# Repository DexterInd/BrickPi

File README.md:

BrickPi
=====

This project combines the brains of a Raspberry Pi with the brawn of a LEGO MINDSTORMS NXT.  Read more about it here:  http://www.dexterindustries.com/BrickPi

These files have been made available online through a [Creative Commons Attribution-ShareAlike 3.0](http://creativecommons.org/licenses/by-sa/3.0/) license.

## Compatibility
This repository is for the BrickPi and BrickPi+. For the BrickPi3 (hardware version 3.x.x) see the [BrickPi3 repository](https://github.com/DexterInd/BrickPi3).

## Getting Started
We've devoted some serious time to trying to make sure that it's easy to get started.  If you're lost, we would like to first direct you to our [website for the BrickPi](http://www.dexterindustries.com/BrickPi/getting-started/).

## Quick Install

In order to quick install the `BrickPi` repository, open up a terminal and type the following command:
```
sudo curl -kL dexterindustries.com/update_brickpi_plus | bash
```
The same command can be used for updating the `BrickPi` to the latest version.

## This Repository
This repository holds firmware and hardware designs, as well as software examples for Python, C, and Scratch.  

## Image for the SD Card
Our custom image for the Raspberry Pi makes using the BrickPi easy.  We've modified the standard Raspbian a little bit.  You can download the latest image here [on our getting started section.](https://www.dexterindustries.com/howto/install-raspbian-for-robots-image-on-an-sd-card/)

## Firmware
The board firmware is made in Arduino in order to make it super-hackable.  The firmware is written in Arduino 1.0 and can be uploaded via an ISP programmer.  It can also be uploaded with an Arduino Uno, with an adapter explained in this repository.

The board supports LEGO NXT motors, EV3 motors, and LEGO NXT sensors, as well as many of Dexter Industries sensors for LEGO Mindstorms.

[Dexter Industries](http://www.dexterindustries.com/)
[BrickPi for the Raspberry Pi](http://www.dexterindustries.com/BrickPi)

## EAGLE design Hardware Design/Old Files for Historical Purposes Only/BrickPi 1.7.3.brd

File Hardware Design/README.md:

BrickPi Hardware
=====

Read [more about the BrickPi here](http://www.dexterindustries.com/BrickPi)

These files have been made available online through a [Creative Commons Attribution-ShareAlike 3.0](http://creativecommons.org/licenses/by-sa/3.0/) license.

## Getting Started

We've devoted some effort to making sure that it's easy to get started.  If you're lost, we would like to first direct you to our [website for the BrickPi](http://www.dexterindustries.com/BrickPi/)

## This Repository

This repository only holds our latest hardware designs.  

[Dexter Industries](http://www.dexterindustries.com/)
[BrickPi](http://www.dexterindustries.com/BrickPi)

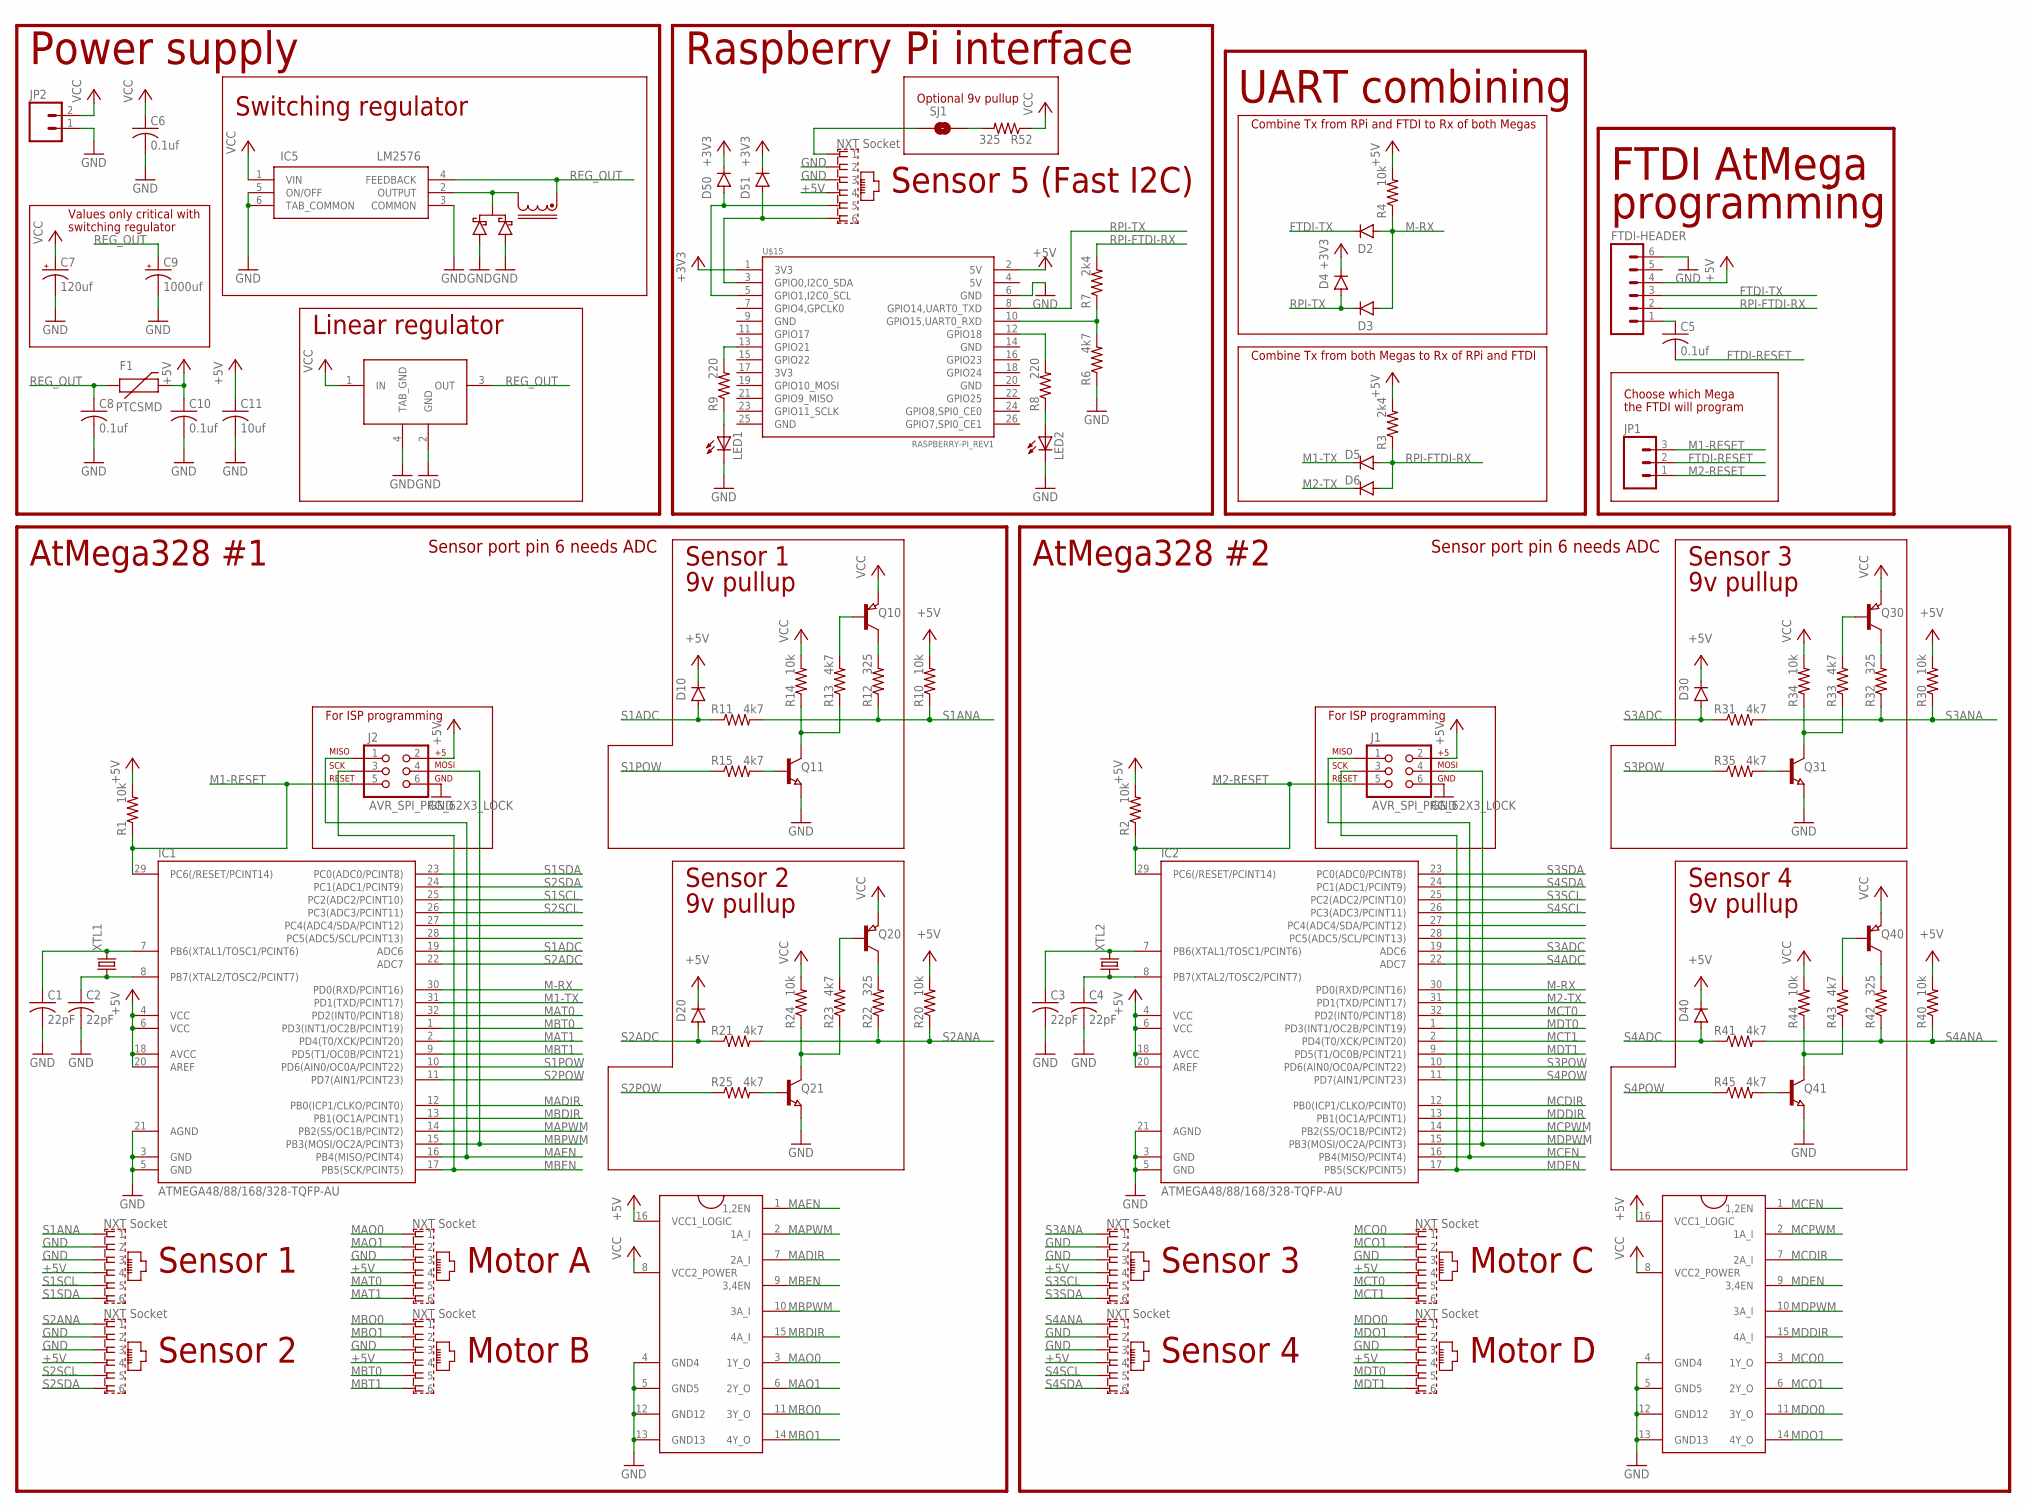
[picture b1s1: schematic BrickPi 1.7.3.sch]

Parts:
C1, C2, C3, C4: 22pF; C0805
C5, C6, C8, C10: 0.1uf; C0805
C7: 120uf; E2,5-6
C9: 1000uf; E3,5-10
C11: 10uf; C0805
D1: DIODE_SCHOTTKY_VS-6CWQ04FNTRPBF; DPAK
D2, D3, D4, D5, D6, D10, D20, D30, D40, D50, D51: DIODESOD80; SOD80
F1: PTCSMD; PTC-1206
FTDI-HEADER: M06LOCK; 1X06_LOCK
IC1, IC2: ATMEGA48/88/168/328-TQFP-AU; TQFP32-08
IC3, IC4: SN754410; DIL16-ROUND-HEAT_DIS_SN754410
IC5: LM2576; TO220-5-H
IC6: REGULATOR_5V_TO220-H_7805; TO220-H
J1, J2: AVR_SPI_PRG_62X3_LOCK; 2X3_LOCK
JP1: M03LOCK; 1X03_LOCK
JP2: M02LOCK; 1X02_LOCK
LED1, LED2: LED0805; 0805-LED
Q10, Q20, Q30, Q40: PNP-TRANSISTOR_SOT23; SOT23
Q11, Q21, Q31, Q41: NPN-TRANSISTOR_SOT23; SOT23
R1, R2, R4, R10, R14, R20, R24, R30, R34, R40, R44: 10k; 0603
R3, R7: 2k4; 0603
R6, R11, R13, R15, R21, R23, R25, R31, R33, R35, R41, R43, R45: 4k7; 0603
R8, R9: 220; 0603
R12, R22, R32, R42, R52: 325; 1206
SJ1: SOLDERJUMPERNO; SJ_2
U$3, U$4, U$5, U$7, U$8, U$9, U$10, U$11, U$12: NXT-SOCKETREGULAR; NXT-SOCKET
U$14: INDUCTOR_PULSE_P0250.XXXNL
U$15: RASPBERRY-PI_REV1
XTL1, XTL2: CRYSTALHC49S; HC49/S

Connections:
+3V3: D4.C, D50.C, D51.C, U$15.1 (3V3)
+5V: C10.1, C11.1, D10.C, D20.C, D30.C, D40.C, F1.2, FTDI-HEADER.4, IC1.4 (VCC), IC1.6 (VCC), IC1.18 (AVCC), IC1.20 (AREF), IC2.4 (VCC), IC2.6 (VCC), IC2.18 (AVCC), IC2.20 (AREF), IC3.16 (VCC1_LOGIC), IC4.16 (VCC1_LOGIC), J1.2, J2.2, R1.2, R2.2, R3.2, R4.2, R10.2, R20.2, R30.2, R40.2, U$3.4, U$4.4, U$5.4, U$7.4, U$8.4, U$9.4, U$10.4, U$11.4, U$12.4, U$15.2 (5V)
FTDI-RESET: C5.2, JP1.2
FTDI-TX: D2.C, FTDI-HEADER.3
GND: C1.2, C2.2, C3.2, C4.2, C6.2, C7.-, C8.2, C9.-, C10.2, C11.2, D1.1, D1.3, FTDI-HEADER.6, IC1.3 (GND), IC1.5 (GND), IC1.21 (AGND), IC2.3 (GND), IC2.5 (GND), IC2.21 (AGND), IC3.4 (GND4), IC3.5 (GND5), IC3.12 (GND12), IC3.13 (GND13), IC4.4 (GND4), IC4.5 (GND5), IC4.12 (GND12), IC4.13 (GND13), IC5.3 (COMMON), IC5.5 (ON/OFF), IC5.6 (TAB_COMMON), IC6.2 (GND), IC6.4 (TAB_GND), J1.6, J2.6, JP2.1, LED1.2 (C), LED2.2 (C), Q11.2 (E), Q21.2 (E), Q31.2 (E), Q41.2 (E), R6.1, U$3.3, U$4.3, U$5.3, U$7.3, U$8.2, U$8.3, U$9.2, U$9.3, U$10.2, U$10.3, U$11.2, U$11.3, U$12.2, U$12.3, U$15.6 (GND)
M1-RESET: IC1.29 (PC6(/RESET/PCINT14)), J2.5, JP1.3, R1.1
M1-TX: D5.C, IC1.31 (PD1(TXD/PCINT17))
M2-RESET: IC2.29 (PC6(/RESET/PCINT14)), J1.5, JP1.1, R2.1
M2-TX: D6.C, IC2.31 (PD1(TXD/PCINT17))
M-RX: D2.A, D3.A, IC1.30 (PD0(RXD/PCINT16)), IC2.30 (PD0(RXD/PCINT16)), R4.1
MADIR: IC1.12 (PB0(ICP1/CLKO/PCINT0)), IC3.7 (2A_I)
MAEN: IC1.16 (PB4(MISO/PCINT4)), IC3.1 (1,2EN), J2.1
MAO0: IC3.3 (1Y_O), U$3.1
MAO1: IC3.6 (2Y_O), U$3.2
MAPWM: IC1.14 (PB2(SS/OC1B/PCINT2)), IC3.2 (1A_I)
MAT0: IC1.32 (PD2(INT0/PCINT18)), U$3.5
MAT1: IC1.2 (PD4(T0/XCK/PCINT20)), U$3.6
MBDIR: IC1.13 (PB1(OC1A/PCINT1)), IC3.15 (4A_I)
MBEN: IC1.17 (PB5(SCK/PCINT5)), IC3.9 (3,4EN), J2.3
MBO0: IC3.11 (3Y_O), U$4.1
MBO1: IC3.14 (4Y_O), U$4.2
MBPWM: IC1.15 (PB3(MOSI/OC2A/PCINT3)), IC3.10 (3A_I), J2.4
MBT0: IC1.1 (PD3(INT1/OC2B/PCINT19)), U$4.5
MBT1: IC1.9 (PD5(T1/OC0B/PCINT21)), U$4.6
MCDIR: IC2.12 (PB0(ICP1/CLKO/PCINT0)), IC4.7 (2A_I)
MCEN: IC2.16 (PB4(MISO/PCINT4)), IC4.1 (1,2EN), J1.1
MCO0: IC4.3 (1Y_O), U$5.1
MCO1: IC4.6 (2Y_O), U$5.2
MCPWM: IC2.14 (PB2(SS/OC1B/PCINT2)), IC4.2 (1A_I)
MCT0: IC2.32 (PD2(INT0/PCINT18)), U$5.5
MCT1: IC2.2 (PD4(T0/XCK/PCINT20)), U$5.6
MDDIR: IC2.13 (PB1(OC1A/PCINT1)), IC4.15 (4A_I)
MDEN: IC2.17 (PB5(SCK/PCINT5)), IC4.9 (3,4EN), J1.3
MDO0: IC4.11 (3Y_O), U$7.1
MDO1: IC4.14 (4Y_O), U$7.2
MDPWM: IC2.15 (PB3(MOSI/OC2A/PCINT3)), IC4.10 (3A_I), J1.4
MDT0: IC2.1 (PD3(INT1/OC2B/PCINT19)), U$7.5
MDT1: IC2.9 (PD5(T1/OC0B/PCINT21)), U$7.6
unnamed: D1.4, IC5.2 (OUTPUT), U$14.P$2
unnamed: C5.1, FTDI-HEADER.1
unnamed: LED2.1 (A), R8.1
unnamed: LED1.1 (A), R9.1
unnamed: C1.1, IC1.7 (PB6(XTAL1/TOSC1/PCINT6)), XTL1.2
unnamed: R9.2, U$15.13 (GPIO21)
unnamed: C2.1, IC1.8 (PB7(XTAL2/TOSC2/PCINT7)), XTL1.1
unnamed: Q11.1 (B), R15.2
unnamed: Q20.3 (C), R22.2
unnamed: Q21.1 (B), R25.2
unnamed: R6.2, R7.1, U$15.10 (GPIO15,UART0_RXD)
unnamed: R8.2, U$15.12 (GPIO18)
unnamed: Q11.3 (C), R13.1, R14.1
unnamed: C3.1, IC2.7 (PB6(XTAL1/TOSC1/PCINT6)), XTL2.2
unnamed: C4.1, IC2.8 (PB7(XTAL2/TOSC2/PCINT7)), XTL2.1
unnamed: Q21.3 (C), R23.1, R24.1
unnamed: Q20.1 (B), R23.2
unnamed: Q30.3 (C), R32.2
unnamed: Q31.1 (B), R35.2
unnamed: Q10.1 (B), R13.2
unnamed: Q31.3 (C), R33.1, R34.1
unnamed: Q30.1 (B), R33.2
unnamed: Q10.3 (C), R12.2
unnamed: Q40.3 (C), R42.2
unnamed: SJ1.1, U$12.1
unnamed: R52.2, SJ1.2
unnamed: D51.A, U$12.6, U$15.3 (GPIO0,I2C0_SDA)
unnamed: D50.A, U$12.5, U$15.5 (GPIO1,I2C0_SCL)
unnamed: Q41.1 (B), R45.2
unnamed: Q41.3 (C), R43.1, R44.1
unnamed: Q40.1 (B), R43.2
REG_OUT: C8.1, C9.+, F1.1, IC5.4 (FEEDBACK), IC6.3 (OUT), U$14.P$1
RPI-FTDI-RX: D5.A, D6.A, FTDI-HEADER.2, R3.1, R7.2
RPI-TX: D3.C, D4.A, U$15.8 (GPIO14,UART0_TXD)
S1ADC: D10.A, IC1.19 (ADC6), R11.1
S1ANA: R10.1, R11.2, R12.1, U$8.1
S1POW: IC1.10 (PD6(AIN0/OC0A/PCINT22)), R15.1
S1SCL: IC1.25 (PC2(ADC2/PCINT10)), U$8.5
S1SDA: IC1.23 (PC0(ADC0/PCINT8)), U$8.6
S2ADC: D20.A, IC1.22 (ADC7), R21.1
S2ANA: R20.1, R21.2, R22.1, U$9.1
S2POW: IC1.11 (PD7(AIN1/PCINT23)), R25.1
S2SCL: IC1.26 (PC3(ADC3/PCINT11)), U$9.5
S2SDA: IC1.24 (PC1(ADC1/PCINT9)), U$9.6
S3ADC: D30.A, IC2.19 (ADC6), R31.1
S3ANA: R30.1, R31.2, R32.1, U$10.1
S3POW: IC2.10 (PD6(AIN0/OC0A/PCINT22)), R35.1
S3SCL: IC2.25 (PC2(ADC2/PCINT10)), U$10.5
S3SDA: IC2.23 (PC0(ADC0/PCINT8)), U$10.6
S4ADC: D40.A, IC2.22 (ADC7), R41.1
S4ANA: R40.1, R41.2, R42.1, U$11.1
S4POW: IC2.11 (PD7(AIN1/PCINT23)), R45.1
S4SCL: IC2.26 (PC3(ADC3/PCINT11)), U$11.5
S4SDA: IC2.24 (PC1(ADC1/PCINT9)), U$11.6
VCC: C6.1, C7.+, IC3.8 (VCC2_POWER), IC4.8 (VCC2_POWER), IC5.1 (VIN), IC6.1 (IN), JP2.2, Q10.2 (E), Q20.2 (E), Q30.2 (E), Q40.2 (E), R14.2, R24.2, R34.2, R44.2, R52.1

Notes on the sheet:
Sensor 1
Motor A
Motor B
Sensor 5 (Fast I2C)
Sensor port pin 6 needs ADC
Sensor 2
Sensor 3
Motor C
Motor D
Sensor 4
Choose which Mega
the FTDI will program
Combine Tx from RPi and FTDI to Rx of both Megas
Combine Tx from both Megas to Rx of RPi and FTDI
Linear regulator
Switching regulator
Values only critical with
switching regulator
Power supply
FTDI AtMega
UART combining
9v pullup
AtMega328 #1
For ISP programming
AtMega328 #2
Raspberry Pi interface
programming
Optional 9v pullup

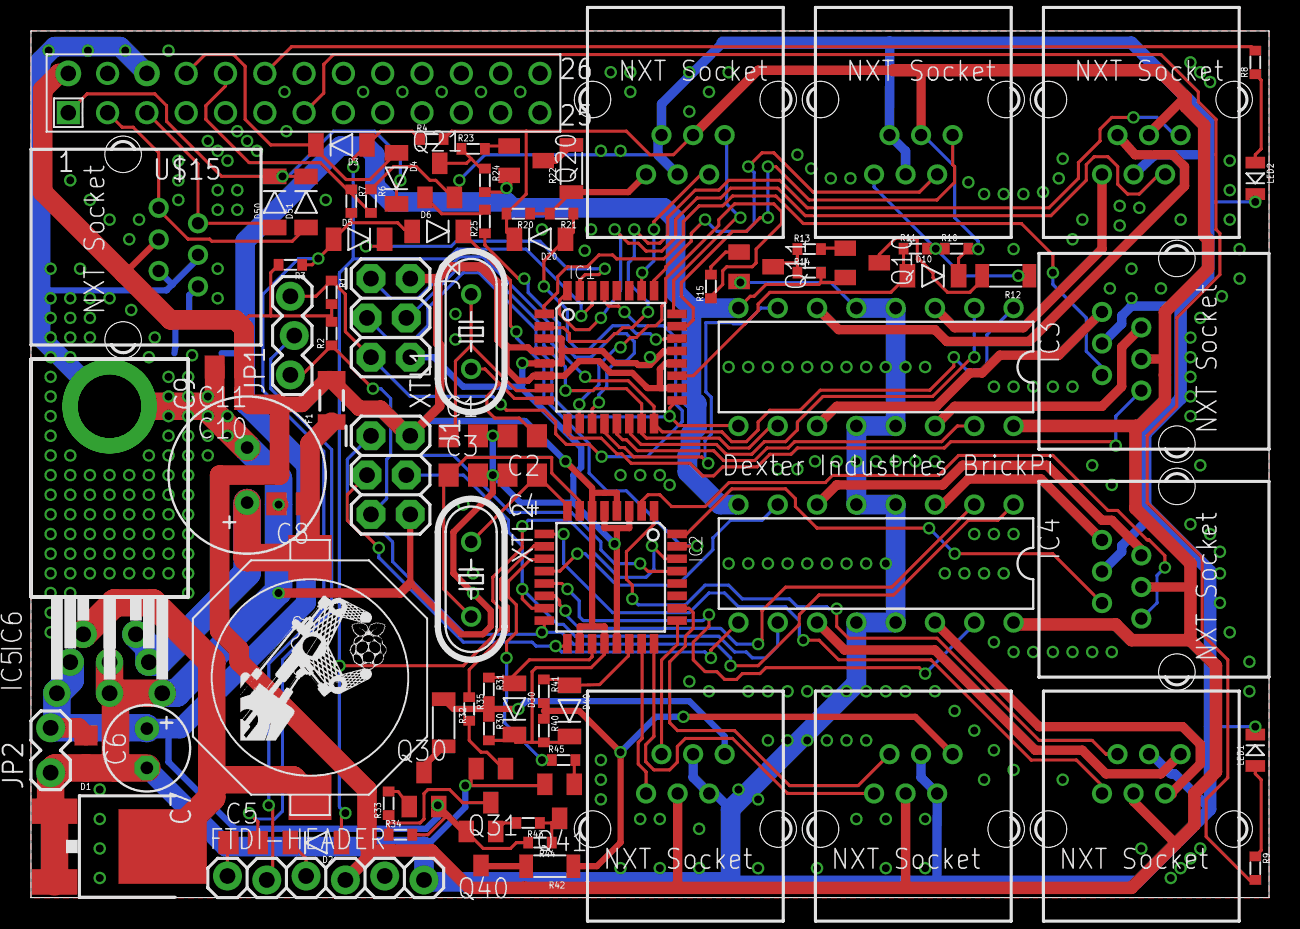
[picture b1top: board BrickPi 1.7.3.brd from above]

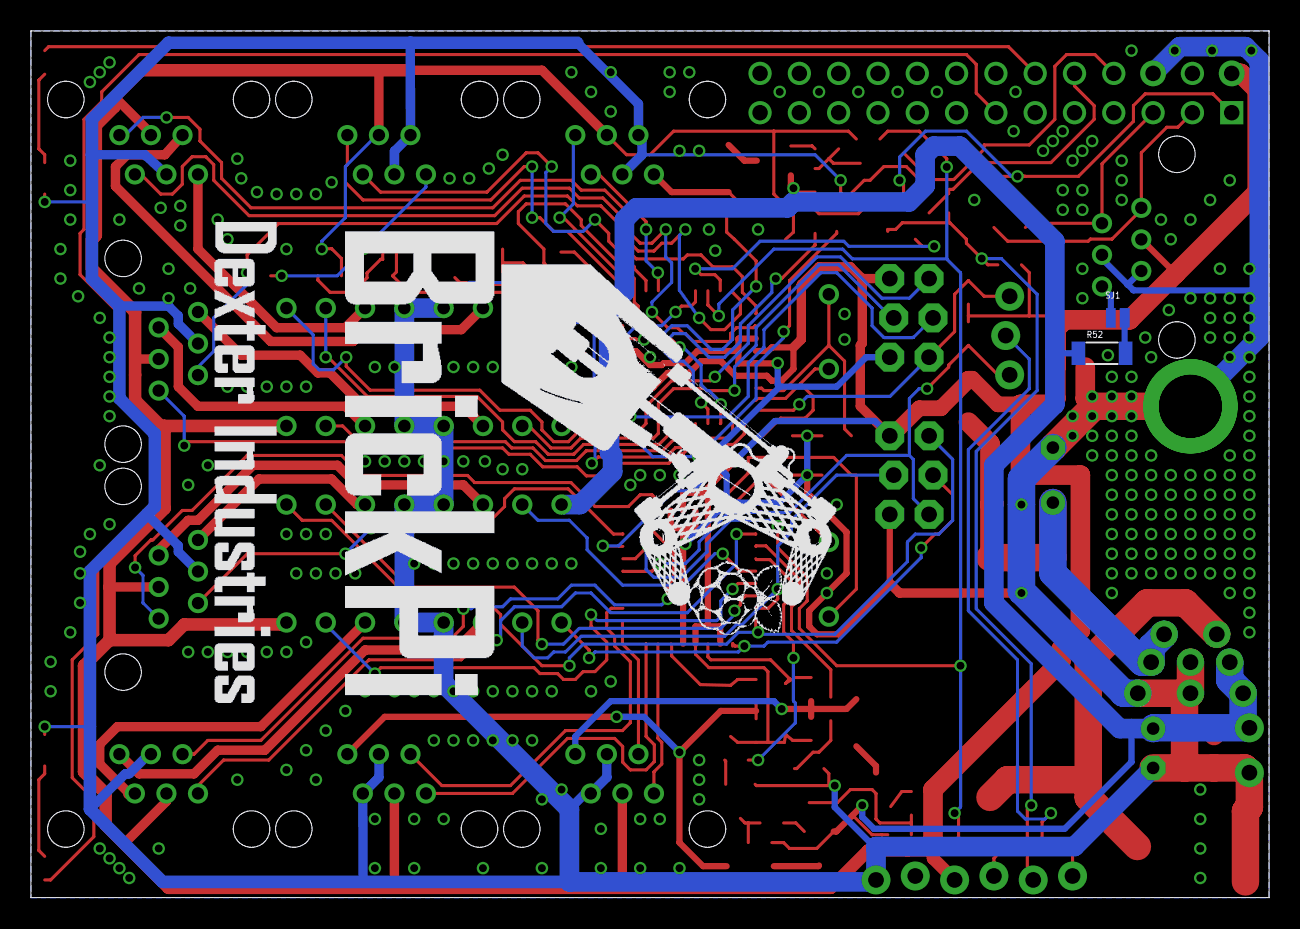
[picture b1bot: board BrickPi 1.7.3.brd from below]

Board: 2 copper layers, 80.0 x 56.0 mm, 92 parts (2 on the bottom side), 93 nets.

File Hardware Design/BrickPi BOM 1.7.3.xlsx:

Part | Value | Device | Package | Description | Part Number and Link
C1 | 22 pF | C-USC0805 | C0805 | Capacitor | VJ0805A220GXAPW1BC
C2 | 22 pF | C-USC0805 | C0805 | Capacitor | VJ0805A220GXAPW1BC
C3 | 22 pF | C-USC0805 | C0805 | Capacitor | VJ0805A220GXAPW1BC
C4 | 22 pF | C-USC0805 | C0805 | Capacitor | VJ0805A220GXAPW1BC
C5 | 0.1 uF | C-USC0805 | C0805 | Capacitor | VJ0805V104MXBPW1BC
C6 | 0.1 uF | C-USC0805 | C0805 | Capacitor | VJ0805V104MXBPW1BC
C8 | 0.1 uF | C-USC0805 | C0805 | Capacitor | VJ0805V104MXBPW1BC
C10 | 0.1 uF | C-USC0805 | C0805 | Capacitor | VJ0805V104MXBPW1BC
C11 | 10uf | C-USC0805 | C0805 | CAPACITOR, American symbol | CGA4J1X5R1C106K
D2 |  | DIODE-SOD80C | SOD80C | DIODE | LS4448GS08
D3 |  | DIODE-SOD80C | SOD80C | DIODE | LS4448GS09
D4 |  | DIODE-SOD80C | SOD80C | DIODE | LS4448GS10
D5 |  | DIODE-SOD80C | SOD80C | DIODE | LS4448GS11
D6 |  | DIODE-SOD80C | SOD80C | DIODE | LS4448GS12
D10 |  | DIODE-SOD80C | SOD80C | DIODE | LS4448GS13
D20 |  | DIODE-SOD80C | SOD80C | DIODE | LS4448GS14
D30 |  | DIODE-SOD80C | SOD80C | DIODE | LS4448GS15
D40 |  | DIODE-SOD80C | SOD80C | DIODE | LS4448GS16
D50 |  | DIODE-SOD80C | SOD80C | DIODE | LS4448GS15
D51 |  | DIODE-SOD80C | SOD80C | DIODE | LS4448GS16
F1 | PTCSMD | PTCSMD | PTC-1206 | Resettable Fuse PTC | PTS12066V110
IC1 |  | ATMEGA328P-AU | TQFP32-08 | Arduino | ATMEGA328P-AU
IC2 |  | ATMEGA328P-AU | TQFP32-08 | Arduino | ATMEGA328P-AU
IC3 | SN754410 | DIL16-ROUND-HEAT_DIS_SN754410 |  |  | SN754410NE
IC4 | SN754410 | DIL16-ROUND-HEAT_DIS_SN754410 |  |  | SN754410NE
IC6 | REGULATOR_5V_TO220-H_7805 | REGULATOR_5V_TO220-H_7805 | TO220-H | Positive VOLTAGE REGULATOR | 512-LM7805ACT
JP2 |  | M02LOCK | 1X02_LOCK | Header 2 | 538-22-23-2021
LED1 |  | LED0805 | 0805-LED | LEDs | 638-172BHC-AN1P23T
LED2 |  | LED0805 | 0805-LED | LEDs | 638-172BHC-AN1P23T
Q10 |  | PNP-TRANSISTOR_SOT23 | SOT23 | PNP TRANSISTOR | MMBT3906LT3G
Q11 |  | NPN-TRANSISTOR_SOT23 | SOT23 | NPN TRANSISTOR | MMBT3904
Q20 |  | PNP-TRANSISTOR_SOT23 | SOT23 | PNP TRANSISTOR | MMBT3906LT3G
Q21 |  | NPN-TRANSISTOR_SOT23 | SOT23 | NPN TRANSISTOR | MMBT3904
Q30 |  | PNP-TRANSISTOR_SOT23 | SOT23 | PNP TRANSISTOR | MMBT3906LT3G
Q31 |  | NPN-TRANSISTOR_SOT23 | SOT23 | NPN TRANSISTOR | MMBT3904
Q40 |  | PNP-TRANSISTOR_SOT23 | SOT23 | PNP TRANSISTOR | MMBT3906LT3G
Q41 |  | NPN-TRANSISTOR_SOT23 | SOT23 | NPN TRANSISTOR | MMBT3904
XTL1 |  | CRYSTALHC49S | HC49/S | CRYSTAL | ATS16B
XTL2 |  | CRYSTALHC49S | HC49/S | CRYSTAL | ATS16B
U$3 |  | NXT-SOCKETREGULAR | NXT-SOCKETREGULAR | NXT-SOCKET | Female Sockets
U$4 |  | NXT-SOCKETREGULAR | NXT-SOCKETREGULAR | NXT-SOCKET | Female Sockets
U$5 |  | NXT-SOCKETREGULAR | NXT-SOCKETREGULAR | NXT-SOCKET | Female Sockets
U$7 |  | NXT-SOCKETREGULAR | NXT-SOCKETREGULAR | NXT-SOCKET | Female Sockets
U$8 |  | NXT-SOCKETREGULAR | NXT-SOCKETREGULAR | NXT-SOCKET | Female Sockets
U$9 |  | NXT-SOCKETREGULAR | NXT-SOCKETREGULAR | NXT-SOCKET | Female Sockets
U$10 |  | NXT-SOCKETREGULAR | NXT-SOCKETREGULAR | NXT-SOCKET | Female Sockets
U$11 |  | NXT-SOCKETREGULAR | NXT-SOCKETREGULAR | NXT-SOCKET | Female Sockets
U$12 |  | NXT-SOCKETREGULAR | NXT-SOCKETREGULAR | NXT-SOCKET | Female Sockets
R1 | 10k | RESISTOR0603-RES | 603 | Resistor | RK73B1JTTDD103J
R2 | 10k | RESISTOR0603-RES | 603 | Resistor | RK73B1JTTDD103J
R3 | 2k4 | RESISTOR0603-RES | 603 | Resistor | RK73B1JTTDD242J
R4 | 10k | RESISTOR0603-RES | 603 | Resistor | RK73B1JTTDD103J
R6 | 4k7 | RESISTOR0603-RES | 603 | Resistor | RK73B1JTTDD472J
R7 | 2k4 | RESISTOR0603-RES | 603 | Resistor | RK73B1JTTDD242J
R8 | 220 | RESISTOR0603-RES | 603 | Resistor | RK73B1JTTDD221J
R9 | 220 | RESISTOR0603-RES | 603 | Resistor | RK73B1JTTDD221J
R10 | 10k | RESISTOR0603-RES | 603 | Resistor | RK73B1JTTDD103J
R11 | 4k7 | RESISTOR0603-RES | 603 | Resistor | RK73B1JTTDD472J
R12 | 325 | RESISTOR1206 | 1206 | Resistor | CR1206-FX-3300ELF
R13 | 4k7 | RESISTOR0603-RES | 603 | Resistor | RK73B1JTTDD472J
R14 | 10k | RESISTOR0603-RES | 603 | Resistor | RK73B1JTTDD103J
R15 | 4k7 | RESISTOR0603-RES | 603 | Resistor | RK73B1JTTDD472J
R20 | 10k | RESISTOR0603-RES | 603 | Resistor | RK73B1JTTDD103J
R21 | 4k7 | RESISTOR0603-RES | 603 | Resistor | RK73B1JTTDD472J
R22 | 325 | RESISTOR1206 | 1206 | Resistor | CR1206-FX-3300ELF
R23 | 4k7 | RESISTOR0603-RES | 603 | Resistor | RK73B1JTTDD472J
R24 | 10k | RESISTOR0603-RES | 603 | Resistor | RK73B1JTTDD103J
R25 | 4k7 | RESISTOR0603-RES | 603 | Resistor | RK73B1JTTDD472J
R30 | 10k | RESISTOR0603-RES | 603 | Resistor | RK73B1JTTDD103J
R31 | 4k7 | RESISTOR0603-RES | 603 | Resistor | RK73B1JTTDD472J
R32 | 325 | RESISTOR1206 | 1206 | Resistor | CR1206-FX-3300ELF
R33 | 4k7 | RESISTOR0603-RES | 603 | Resistor | RK73B1JTTDD472J
R34 | 10k | RESISTOR0603-RES | 603 | Resistor | RK73B1JTTDD103J
R35 | 4k7 | RESISTOR0603-RES | 603 | Resistor | RK73B1JTTDD472J
R40 | 10k | RESISTOR0603-RES | 603 | Resistor | RK73B1JTTDD103J
R41 | 4k7 | RESISTOR0603-RES | 603 | Resistor | RK73B1JTTDD472J
R42 | 325 | RESISTOR1206 | 1206 | Resistor | CR1206-FX-3300ELF
R43 | 4k7 | RESISTOR0603-RES | 603 | Resistor | RK73B1JTTDD472J
R44 | 10k | RESISTOR0603-RES | 603 | Resistor | RK73B1JTTDD103J
R45 | 4k7 | RESISTOR0603-RES | 603 | Resistor | RK73B1JTTDD472J
R52 | 325 | RESISTOR1206 | 1206 | Resistor | NOT FILLED
PI_OUTLINE | RASPBERRY-PI | RASPBERRY-PI | RASPBERRY-PI | Raspberry Pi Adapter | Stacking Header 2x13 Extra Tall
SJ1 | SOLDERJUMPERNO | SOLDERJUMPERNO | SJ_2 | Solder Jumper | NOT FILLED
FTDI-HEADER |  | M06LOCK | 1X06_LOCK | Header 6 | NOT FILLED
J1 | AVR_SPI_PRG_62X3_LOCK | AVR_SPI_PRG_62X3_LOCK | 2X3_LOCK | AVR ISP 6 Pin | NOT FILLED
J2 | AVR_SPI_PRG_62X3_LOCK | AVR_SPI_PRG_62X3_LOCK | 2X3_LOCK | AVR ISP 6 Pin | NOT FILLED
JP1 |  | M03LOCK | 1X03_LOCK | Header 3 | NOT FILLED
C7 | 120uF |  |  |  | NOT FILLED
C9 | 1000uF |  |  |  | NOT FILLED
D1 | DIODE_SCHOTTKY_VS-6CWQ04FNTRPBF | DIODE_SCHOTTKY_VS-6CWQ04FNTRPBF | DPAK |  | NOT FILLED
IC5 | LM2576 |  |  |  | NOT FILLED
U$14 | INDUCTOR_PULSE_P0250.XXXNL | INDUCTOR_PULSE_P0250.XXXNL | INDUCTOR_PULSE_P0250.XXXNL |  | NOT FILLED

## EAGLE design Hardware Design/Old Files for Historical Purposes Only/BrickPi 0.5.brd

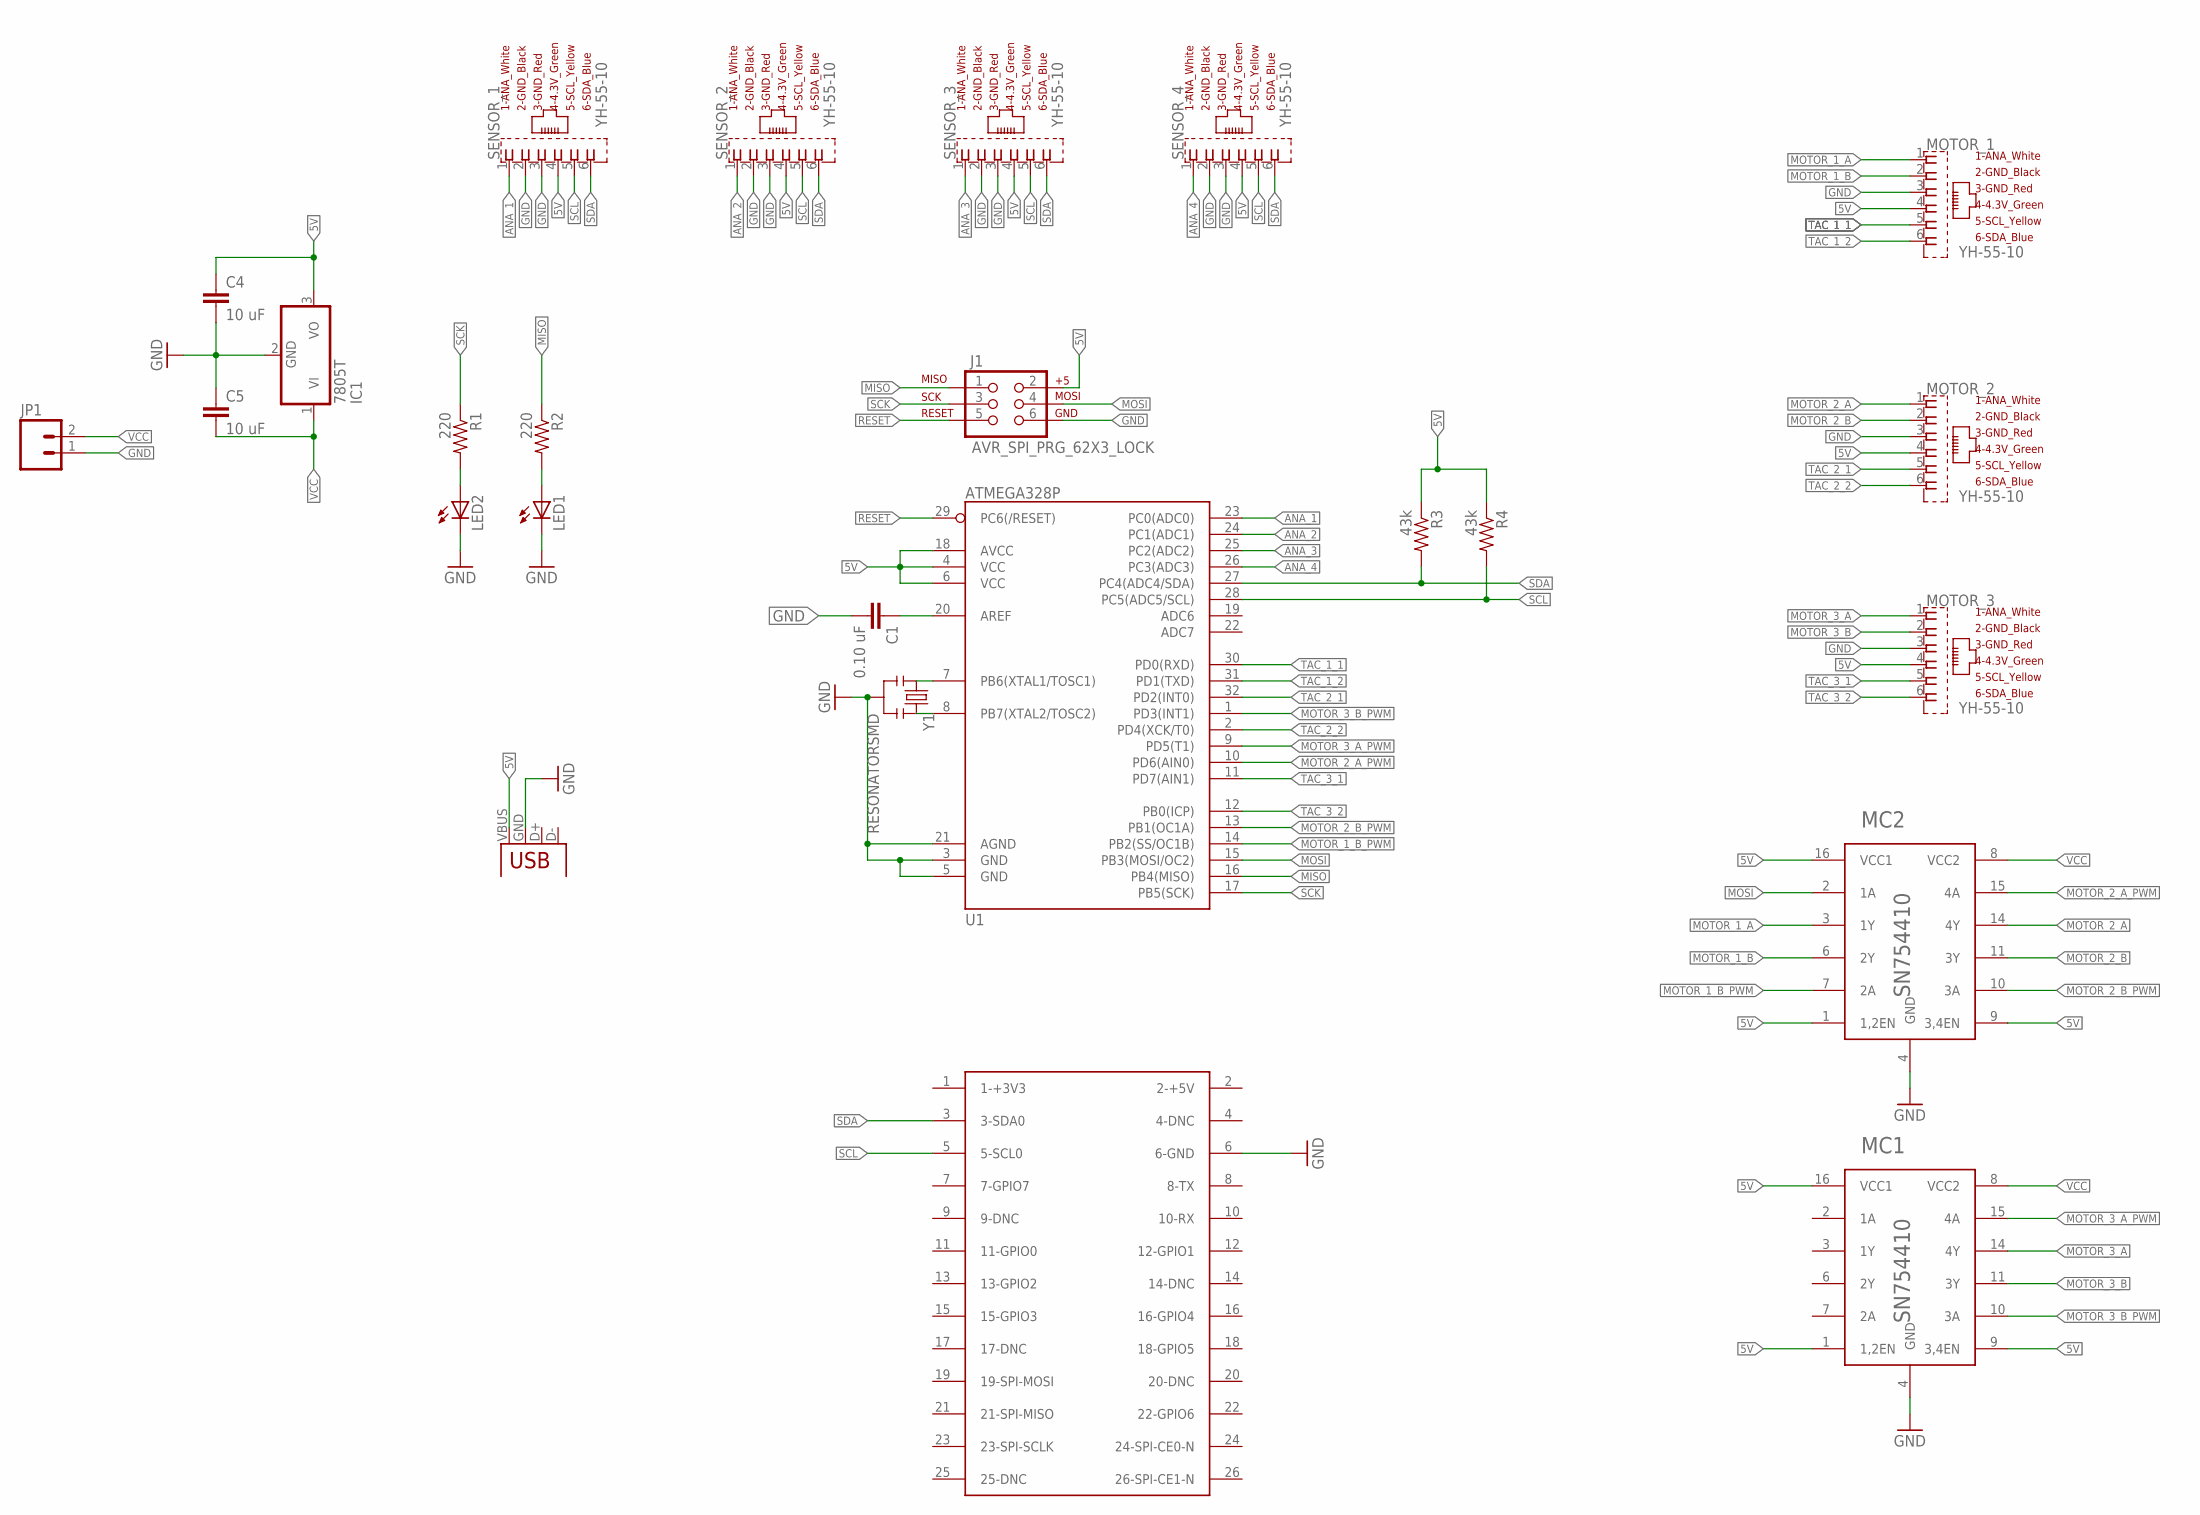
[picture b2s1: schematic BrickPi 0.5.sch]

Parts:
C1: 0.10 uF; 0805
C4, C5: 10 uF; 0805
IC1: 7805T; TO220H
J1: AVR_SPI_PRG_62X3_LOCK; 2X3_LOCK
JP1: M02LOCK; 1X02_LOCK
JP2: USB-A-H
LED1, LED2: LED1206; LED-1206
MC1, MC2: SN754410; DIL16
MOTOR_1, MOTOR_2, MOTOR_3: YH-55-10
PI_OUTLINE: RASPBERRY-PI
R1, R2: 220; 0603-RES
R3, R4: 43k; 0603-RES
SENSOR_1, SENSOR_2, SENSOR_3, SENSOR_4: YH-55-10
U1: ATMEGA328P; TQFP32-08
Y1: RESONATORSMD; RESONATOR-SMD

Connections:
5V: C4.1, IC1.3 (VO), J1.2, JP2.VBUS (GND), MC1.1 (1,2EN), MC1.9 (3,4EN), MC1.16 (VCC1), MC2.1 (1,2EN), MC2.9 (3,4EN), MC2.16 (VCC1), MOTOR_1.4 (4_4.3V_GREEN), MOTOR_2.4 (4_4.3V_GREEN), MOTOR_3.4 (4_4.3V_GREEN), R3.1, R4.1, SENSOR_1.4 (4_4.3V_GREEN), SENSOR_2.4 (4_4.3V_GREEN), SENSOR_3.4 (4_4.3V_GREEN), SENSOR_4.4 (4_4.3V_GREEN), U1.4 (VCC), U1.6 (VCC), U1.18 (AVCC)
ANA_1: SENSOR_1.1 (1_ANA_WHITE), U1.23 (PC0(ADC0))
ANA_2: SENSOR_2.1 (1_ANA_WHITE), U1.24 (PC1(ADC1))
ANA_3: SENSOR_3.1 (1_ANA_WHITE), U1.25 (PC2(ADC2))
ANA_4: SENSOR_4.1 (1_ANA_WHITE), U1.26 (PC3(ADC3))
GND: C1.2, C4.2, C5.1, IC1.2 (GND), J1.6, JP1.1, JP2.GND (VBUS), LED1.C, LED2.C, MC1.4 (GND), MC1.5 (GND), MC1.12 (GND), MC1.13 (GND), MC2.4 (GND), MC2.5 (GND), MC2.12 (GND), MC2.13 (GND), MOTOR_1.3 (3_GND_RED), MOTOR_2.3 (3_GND_RED), MOTOR_3.3 (3_GND_RED), PI_OUTLINE.6 (6-GND), SENSOR_1.2 (2_GND_BLACK), SENSOR_1.3 (3_GND_RED), SENSOR_2.2 (2_GND_BLACK), SENSOR_2.3 (3_GND_RED), SENSOR_3.2 (2_GND_BLACK), SENSOR_3.3 (3_GND_RED), SENSOR_4.2 (2_GND_BLACK), SENSOR_4.3 (3_GND_RED), U1.3 (GND), U1.5 (GND), U1.21 (AGND), Y1.2
MISO: J1.1, R2.1, U1.16 (PB4(MISO))
MOSI: J1.4, MC2.2 (1A), U1.15 (PB3(MOSI/OC2))
MOTOR_1_A: MC2.3 (1Y), MOTOR_1.1 (1_ANA_WHITE)
MOTOR_1_B: MC2.6 (2Y), MOTOR_1.2 (2_GND_BLACK)
MOTOR_1_B_PWM: MC2.7 (2A), U1.14 (PB2(SS/OC1B))
MOTOR_2_A: MC2.14 (4Y), MOTOR_2.1 (1_ANA_WHITE)
MOTOR_2_A_PWM: MC2.15 (4A), U1.10 (PD6(AIN0))
MOTOR_2_B: MC2.11 (3Y), MOTOR_2.2 (2_GND_BLACK)
MOTOR_2_B_PWM: MC2.10 (3A), U1.13 (PB1(OC1A))
MOTOR_3_A: MC1.14 (4Y), MOTOR_3.1 (1_ANA_WHITE)
MOTOR_3_A_PWM: MC1.15 (4A), U1.9 (PD5(T1))
MOTOR_3_B: MC1.11 (3Y), MOTOR_3.2 (2_GND_BLACK)
MOTOR_3_B_PWM: MC1.10 (3A), U1.1 (PD3(INT1))
unnamed: U1.7 (PB6(XTAL1/TOSC1)), Y1.1
unnamed: U1.8 (PB7(XTAL2/TOSC2)), Y1.3
unnamed: LED2.A, R1.2
unnamed: LED1.A, R2.2
unnamed: C1.1, U1.20 (AREF)
RESET: J1.5, U1.29 (PC6(/RESET))
SCK: J1.3, R1.1, U1.17 (PB5(SCK))
SCL: PI_OUTLINE.5 (5-SCL0), R4.2, SENSOR_1.5 (5_SCL_YELLOW), SENSOR_2.5 (5_SCL_YELLOW), SENSOR_3.5 (5_SCL_YELLOW), SENSOR_4.5 (5_SCL_YELLOW), U1.28 (PC5(ADC5/SCL))
SDA: PI_OUTLINE.3 (3-SDA0), R3.2, SENSOR_1.6 (6_SDA_BLUE), SENSOR_2.6 (6_SDA_BLUE), SENSOR_3.6 (6_SDA_BLUE), SENSOR_4.6 (6_SDA_BLUE), U1.27 (PC4(ADC4/SDA))
TAC_1_1: MOTOR_1.5 (5_SCL_YELLOW), U1.30 (PD0(RXD))
TAC_1_2: MOTOR_1.6 (6_SDA_BLUE), U1.31 (PD1(TXD))
TAC_2_1: MOTOR_2.5 (5_SCL_YELLOW), U1.32 (PD2(INT0))
TAC_2_2: MOTOR_2.6 (6_SDA_BLUE), U1.2 (PD4(XCK/T0))
TAC_3_1: MOTOR_3.5 (5_SCL_YELLOW), U1.11 (PD7(AIN1))
TAC_3_2: MOTOR_3.6 (6_SDA_BLUE), U1.12 (PB0(ICP))
VCC: C5.2, IC1.1 (VI), JP1.2, MC1.8 (VCC2), MC2.8 (VCC2)

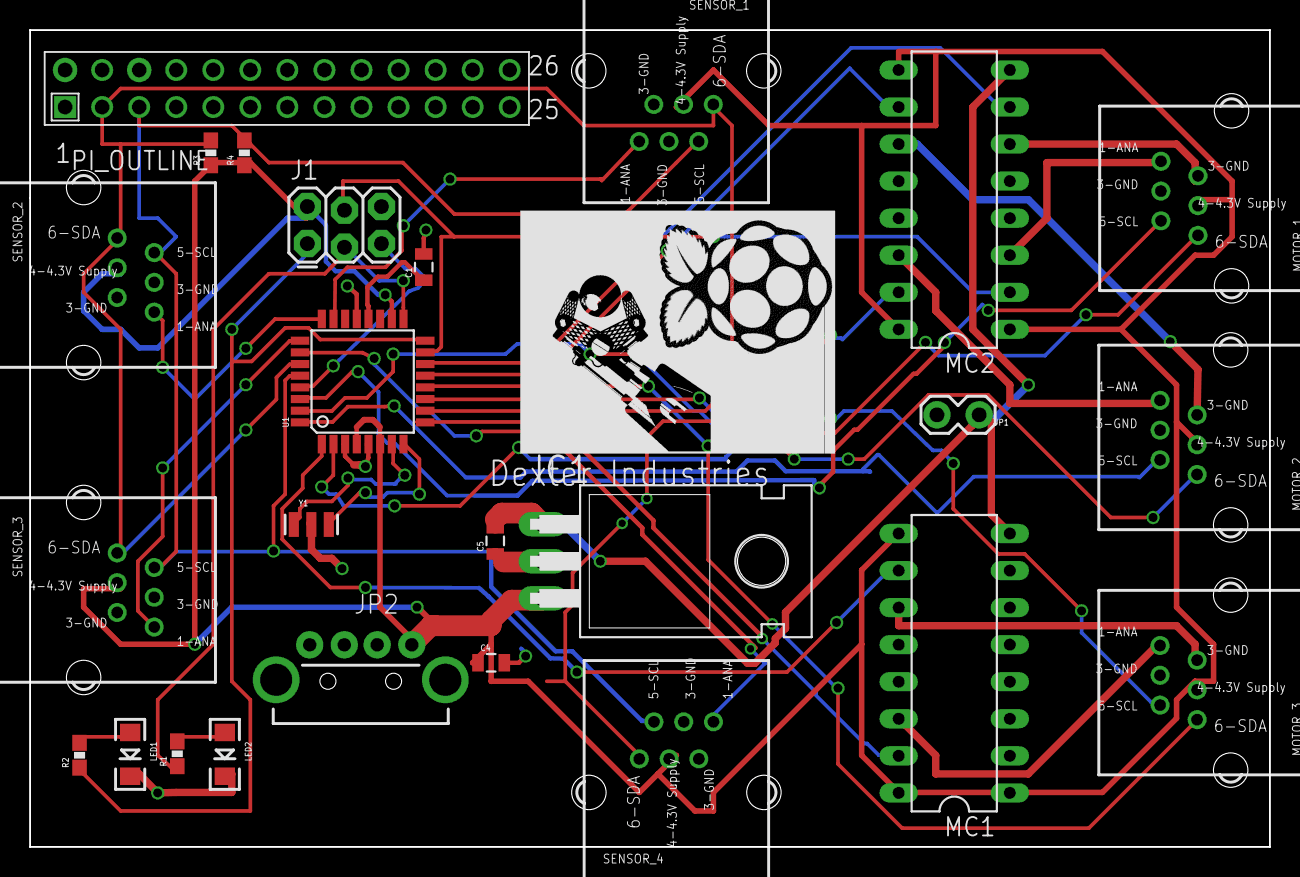
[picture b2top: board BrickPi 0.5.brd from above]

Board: 2 copper layers, 85.0 x 56.0 mm, 25 parts (0 on the bottom side), 35 nets.

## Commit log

2013-03-25 Starting - First commit
    Not fully functional, but functional enough to be dangerous!
2013-04-03 Motors and I2C Sensors Work
2013-04-03 Added hardware files.
    Added the hardware files for Eagle as well as the Todo list for
    implementation!
2013-04-08 Adding the Case Enclosure
    Adding the casing enclosure under "Case Design". Version 2 files went
    in.
2013-04-11 Added Bill of Materials
    Added BOM, some other documents.
2013-05-13 Updated Hardware Design
    Updated the hardware design, adding in Version 0.7, including a BOM.
    The firmware for this new hardware design was updated. The primary
    changes on this version include:
    - Comms between the BrickPi and the Arduino are done via serial.
    - 10k resistors were added to the analog lines on the Arduino chip.
    - And FTDI breakout was added.
2013-05-17 Adding instructions to ignore the "Disable Bootup Info" section in the hobbytronics websites
    Jon recommended to ignore this section as it may interrupt serial communication on the Arduino.
2013-05-17 Add instruction on how to get serial module
    Adding "sudo apt-get install python-serial" so users know where to find the python serial library/module
2013-05-18 Serial Installation
    Added more information on the serial installation method.
2013-06-11 BrickPi_Firmware_2_0 updated with changes in changelog.txt
2013-06-12 firmware supports BrickPi2.WaitForSerial() function
2013-06-27 Added instructions
    Adding some instructions
2013-07-05 Added latest hardware and BOM.
    Also cleaned up the old files and put them into a repository for
    posterity.
2013-07-09 Update Firmware Updated files for firmware update, added some instructions. Added an image folder.
2013-07-09 Clean Up Added latest firmware, instructions for installing it, and cleaned up the older repositories, archived.
2013-07-09 Cleanup.
2013-07-10 Updated some stuff.
2013-07-18 Readme updated.
2013-07-23 Adding wiringpi
2013-08-13 Add models, readmes
2013-08-13 Readme again
2013-08-13 Readme one more time
2013-08-13 Readme tweak
2013-08-13 Update firmware, readme
    Updated firmware, readme.
2013-08-14 Added Ball Shooter
    Added Ball Shooter in LDD. Needs some work but looks great so far.
2013-08-14 Added rclocal and bootup info.
2013-08-27 Update license on Firmware.
    Updated the license on the firmware code.
2013-08-27 Update firmware license again.
2013-08-28 Update firmware, building instructions.
2013-08-28 firmware update
2013-08-28 Added more bom on the models, updates.
2013-09-27 Updated with Schematic
    Updated with Schematic
2013-10-07 Updated pdf schematic
2013-10-07 Updatd something.
2013-10-30 Adding MLCad files for BrickPi
2013-11-05 SimpleBot Lego Designer Files and BOM added
2013-11-05 Adding simple bot build.
2013-11-05 Added Simplebot stuff.
2013-11-05 SimpleBot Readme updated
2013-11-23 Adding balloon info.
2013-11-23 Update readmes
2013-11-24 Updated balloon code!
2013-11-29 Updated Balloon files.
2014-01-07 BrickPi setup script added
2014-01-16 Added script header
2014-01-16 Update install script
2014-01-17 Update script.
2014-01-29 Install script updated and moved to Setup Files
    - apt-get upgrade
    - use custom WiringPi
    - setup.py
2014-03-03 Add Support scripts
2014-03-03 Renamed troubleshooting to support.
2014-03-03 Cleaned up files.
    Cleanup.
2014-03-13 Added script, info for USB loading.
2014-03-17 errors saved to file from the USB mount script
2014-04-08 Updated program.py for USB Bootloader
2014-04-28 Updated Tank Building Instructions
2014-05-01 Updated Tank Design
    Updated LEGO Tank design and zip file.
2014-05-26 Update Image information.
2014-06-04 July 7th Revert
    Reverted the code to July 7th code on BrickPiDev. The previous code was
    holed up in the branch HOLD_MATTS_CODE in case we have to come back.
    But this code compiles and goes on the Arduino of the BrickPi.
2014-06-05 Added Firmware 2.0
    Added firmware 2.0 branch to start working on EV3 firmware.
2014-06-05 Updated changes made to image.
2014-06-06 Change log on recent image update.
2014-06-08 Firmware 2.0 updated to support EV3 Sensors
2014-06-10 Added hints and tricks to compiling.
    Added some hints and tricks to compiling new firmware.
2014-06-12 Added Resizeimage.pl
    Function added for reducing the image size. Really useful tool.
2014-06-13 Update notes on reducing image size.
2014-06-17 Updated the batch file to take COM port from user
2014-06-18 Touch Sensor Working
    Touch sensor is working. Still need work in IR buttons.
2014-06-19 Commenting on the BrickPi EV3 Firmware.
    Added some commenting and cleaned up the firmware.
2014-06-19 Debounce and Versioning.
    EV3 Debounce and NXT Debounce code added.
    Versioning Test added.
2014-06-20 Firmware update script modifications
2014-06-20 Update Firmware Section
    Updated the firmware section with new Readmes and developer notes.
2014-07-01 EV3 touch- (FW) averaging to remove noise
2014-07-03 Firmware Includes Bootloader
    Firmware now includes bootloader.
2014-07-03 Readme.
2014-07-24 Added Arduino Upload Scripts
    Scripts for firmware uploading from Raspberry Pi to BrickPi.
2014-07-24 Updated AVR Programmer script for Firmware
    Updated AVR Programmer script for Firmware, removed everything else.
    From here out we're only using the Pi to program firmware.
2014-07-25 Added EERPOM back in
    Doh! Deleted by accident.
2014-07-30 change log update
2014-08-05 Update change logt, dev notes.
    Added some more notes on reducing the image size.
2014-08-09 Small firmware touchup.
    Firmware 2.0 had some git trash and markup in it.
2014-09-15 Remove duplicated debounce variable
    Removed debounce variable from BrickPiA.
2014-12-30 Walle model added.
2015-04-19 Use markdown so this file is readable on GitHub.
    Also fixed a couple spelling errors.
2015-07-19 Update setup files.
2015-10-11 Update the install files
    Updated the Install Files. Don't install Scratch, comes with Raspbian
    already installed.
2015-10-19 Update Hardware
2016-01-21 eagle brd designs removed
2016-03-09 Adding Firmware 2.5 Version
2016-03-20 added note for Pi 3
    added simple instructions to readme that disables bluetooth
2016-03-27 Add BrickPi+ Layouts
2016-09-26 avoid orphaned index.html files when testing for internet connectivity
2016-12-07 easier install on Pi3/standard Raspbian
2016-12-07 fixed typo
2016-12-07 fix typo
2016-12-07 change from one sed statement to another - clearly wasn't working as cmdline.txt ended up blank
2017-01-05 Brought Software Over
    Brought Python/C/Scratch into this directory.
2017-01-06 Update BrickPi+ Install Script
    There were no dependencies, but I updated the wiringPi instructions.
2017-01-06 Updating Installation Readme
2017-01-06 Update Python Install Script
    Update the Python Install Script
2017-01-06 Another tweak to install.
2017-01-06 BrickPi+ Install Script Cleanup
    Removed WiringPi and use new install procedure.
    Consolidated Python Installation.
    Updated readme, added in Shoban's Dev notes.
2017-01-06 Improving Install for Python for BrickPi+
    Python install seems to fail.
2017-01-06 Setup Install Correction Paths
    Correcting the Path of Setup Install. Again.
2017-01-06 Install update once again.
2017-01-06 Update Install again
    Keep having trouble with directories with spaces in them.
2017-01-06 Update Documentation
    Generally tried to clean up the documentation around installation.
2017-01-06 Minor formatting
2017-01-06 BrickPi File Locations
    Touched up documentation.
    Changes necessary file locations.
    Updated Readme.
    Noted projects that need link changes on Dexter Website.
2017-01-06 Project Path Touchup
    Touched up the location of some of the pictures in the project readmes.
    Nothing earth shattering here!
2017-01-11 remove dist-upgrade which pulls in Pixel
2017-01-11 bring script up to date with functions_library.sh, wiringpi.sh
2017-01-20 Add graphical error if IR receiver is enabled with BrickPi and Scratch
2017-01-20 Cleaning up subprocess call
2017-01-20 Add error handling, hopefully a bugfix?
2017-01-21 Removing failing import statement
2017-02-19 RPi_Server_Code.py now imports the time module
2017-02-19 Added white-space for looks
2017-03-31 Fixed bug
    Init_val is only modified when deg[i] == 0. Fixed it.
2017-09-09 Adding Bookreader Instructions
2017-09-26 Skipping SSL checks on install command in README
2017-09-26 ref RobertLucian/BrickPi#1 : feature - added readme and update script
2019-01-28 update links to simplebot projects
2019-01-28 fix grammatical error
2019-01-28 update links to simplebot projects (#46)
    * update links to simplebot projects
    * fix grammatical error

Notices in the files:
parts and their libraries:
SparkFun-DigitalIC: Licensing: CC v3.0 Share-Alike You are welcome to use this library for commercial purposes.
